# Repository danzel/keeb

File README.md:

# References

Nice ergogen:
https://ergogen.ceoloide.com/

General everything:
https://github.com/soundmonster/samoklava

Has a 3d print case:
https://github.com/rwalkr/eskarp

Measurements:
[Choc Switch](https://github.com/keyboardio/keyswitch_documentation/blob/master/datasheets/Kailh/CPG135001D01.pdf)
[Raspberry Pi Pico, page 6](https://datasheets.raspberrypi.com/pico/pico-datasheet.pdf)

# Print settings:

100% infill
0.2 layer height

Print 4x of `clip`

# miryoku build

https://github.com/danzel/miryoku_qmk/actions/workflows/build-danzel-keeb.yml
Run workflow

# Parts

https://keebd.com/en-nz/products/6x6x4-3mm-dip-push-button-switch
https://keebd.com/products/24cm-dual-90-degree-nylon-3-5mm-to-3-5mm-male-trrs-cable
https://keebd.com/products/trrs-3-5mm-female-jack-pj-320a
https://keebd.com/products/helios-controller
https://keebd.com/products/ambients-silent-linear-twilight-choc-switches

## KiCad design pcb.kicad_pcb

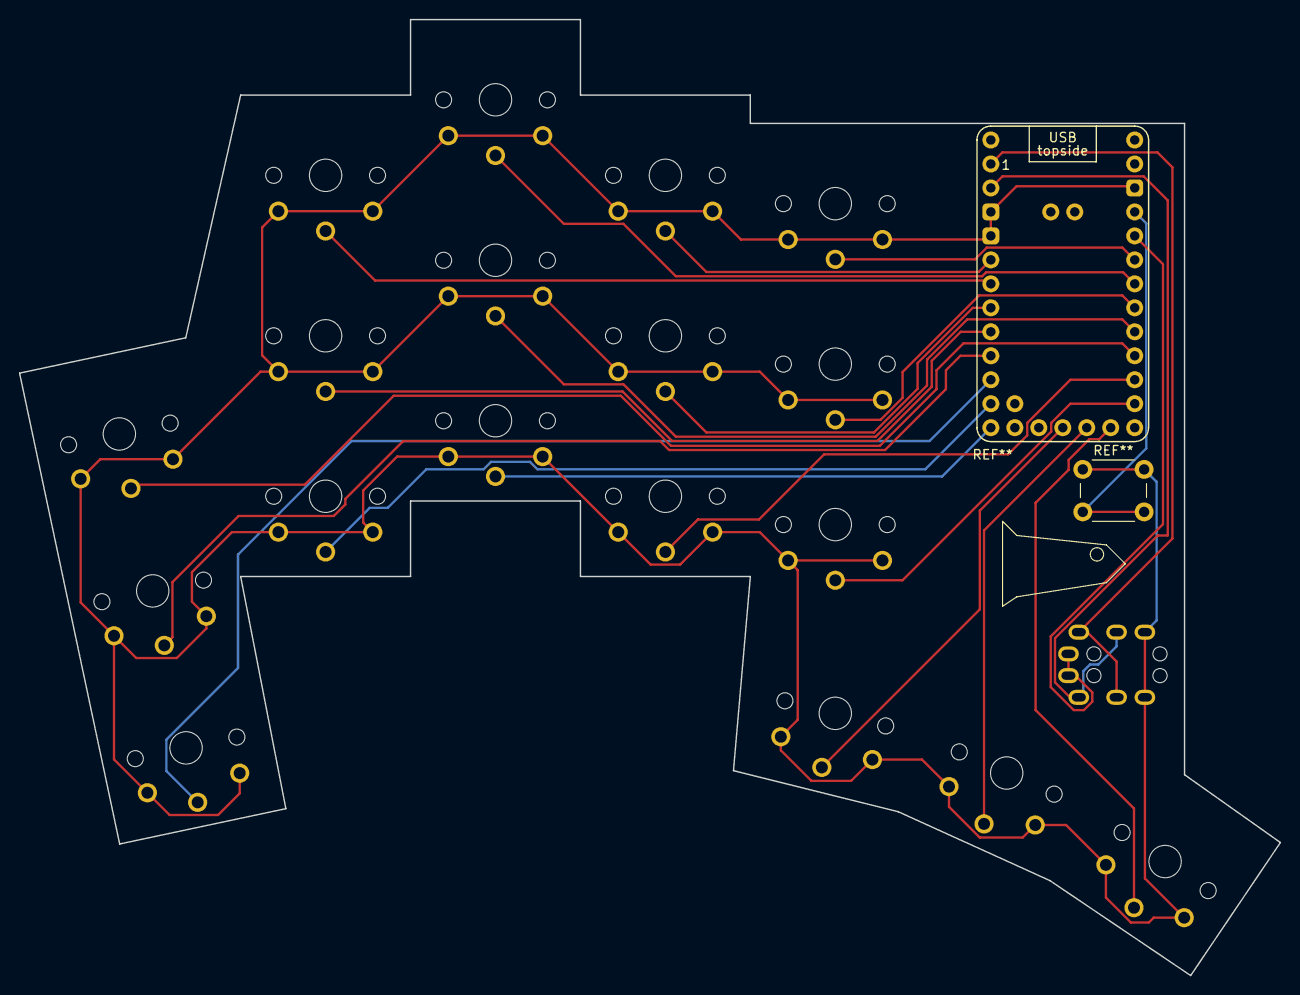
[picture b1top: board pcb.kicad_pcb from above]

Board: 2 copper layers, 133.6 x 101.3 mm, 19 parts (0 on the bottom side), 2 nets.

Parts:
S1, S2, S3, S4, S5, S6, S7, S8, S9, S10, S11, S12, S13, S14, S15, S16, S17, S18: PG1350
TRRS1: TRRS-PJ-320A-dual

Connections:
GND: S1.1, S2.1, S3.1, S4.1, S5.1, S6.1, S7.1, S8.1, S9.1, S10.1, S11.1, S12.1, S13.1, S14.1, S15.1, S16.1, S17.1, S18.1, TRRS1.4
P0: TRRS1.2, TRRS1.3
P1: TRRS1.2, TRRS1.3

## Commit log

2024-07-21 Add initial bits
2024-07-21 lts this way?
2024-07-21 Keep output
2024-07-21 Add README
2024-07-22 More pinky stagger, less thumb splay
2024-07-23 middle -2mm
2024-07-23 link more measurements
2024-07-23 Make the plate thicker around the switches
    Where the clips attach is still thin, but the rest of the plate is the same thickness as the switches from the top of the plate to the bottom flat surface of the switch (before the legs)
2024-07-25 Mounting legs for pico
2024-07-25 Add walls
    The pico legs are too long, will have to make holes in the case for the button and usb to come through
2024-07-26 Add holes for the pico usb and reset to pop through the case
2024-07-26 Fix usb hole size
2024-07-26 Hole for link cable, it can't be as big as it needs to be, might need a resize later
2024-07-26 holes for clips
2024-07-26 Add the bottom base
2024-07-26 Build the base too
2024-07-26 Clip model
2024-07-27 More space beside pico on outside
2024-07-27 Move pico down a bit, it didn't fit as there are tabs at the end of the pcb that aren't in the spec
2024-07-27 USB hole a tiny bit bigger
2024-07-27 Duplicate the reset hole for both sides
2024-07-27 Holes in base for pico mounts are a bit wider, it didn't fit when printed with same size
2024-07-27 Make the area above the pico thinner and move it up in that direction so there is more room for wiring
2024-07-27 Make bottom thickness work for .2 initial layer height
2024-07-27 Update clip for new sizing
2024-07-27 This can be full length actually
2024-07-28 Bottom layer thicker again, this feels good
2024-07-28 Cut usb through the inset wall or it gets in the way when mounting
2024-07-28 Make pico poles smaller so they aren't too tight, slightly more room in their matching piece too
2024-07-28 Tweaked the clip a bit, it fits on now
2024-07-28 Cut the hollow edges, case edge now follows keys instead of the angled bits
    Trying to reduce empty internal volume to reduce noise maybe
2024-07-28 Thicker wall
2024-07-29 Add poles around the keys to hold the plate and base together sort of
2024-07-29 Fix url
2024-07-30 Big redo for a thicker base + misc fixes
    Make the base thicker and put holes for the pins, leaves less room for wiring but hopefully still enough. Hoping that this will reduce the noise when tapping keys.
    Cut a box so you can plug in a usb plug.
2024-08-01 Bigger hole for the link cable to fit the cable I'll try use
2024-08-08 Replace link cable hole with a jumper block
    It is quite close to the rpi, might be nice to make the rpi area of the case wider by 1cm
2024-08-08 Move the jumper header next to the wall to give slightly more room for wiring
2024-08-08 Swap the jumper and bottom clip positions
2024-08-20 Jumper stuff I hadn't committed
2024-08-20 Change thumbsplay, tweaking pinky to be more comfortable maybe
2024-08-20 Slightly thinner bottom of clip, lets it go in without any bulge out
2024-09-18 Splay pinky a touch more
2024-10-16 Start on PCB
2024-10-19 Routed PCB, ergogen has wrong nets
2024-10-30 First go at a base, it's a bit tight no the pcb
2024-10-30 Case as printed
